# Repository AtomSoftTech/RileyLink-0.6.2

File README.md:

# RileyLink-0.6.2

Basically a newer version of : https://github.com/ps2/rileylink/tree/master/hardware

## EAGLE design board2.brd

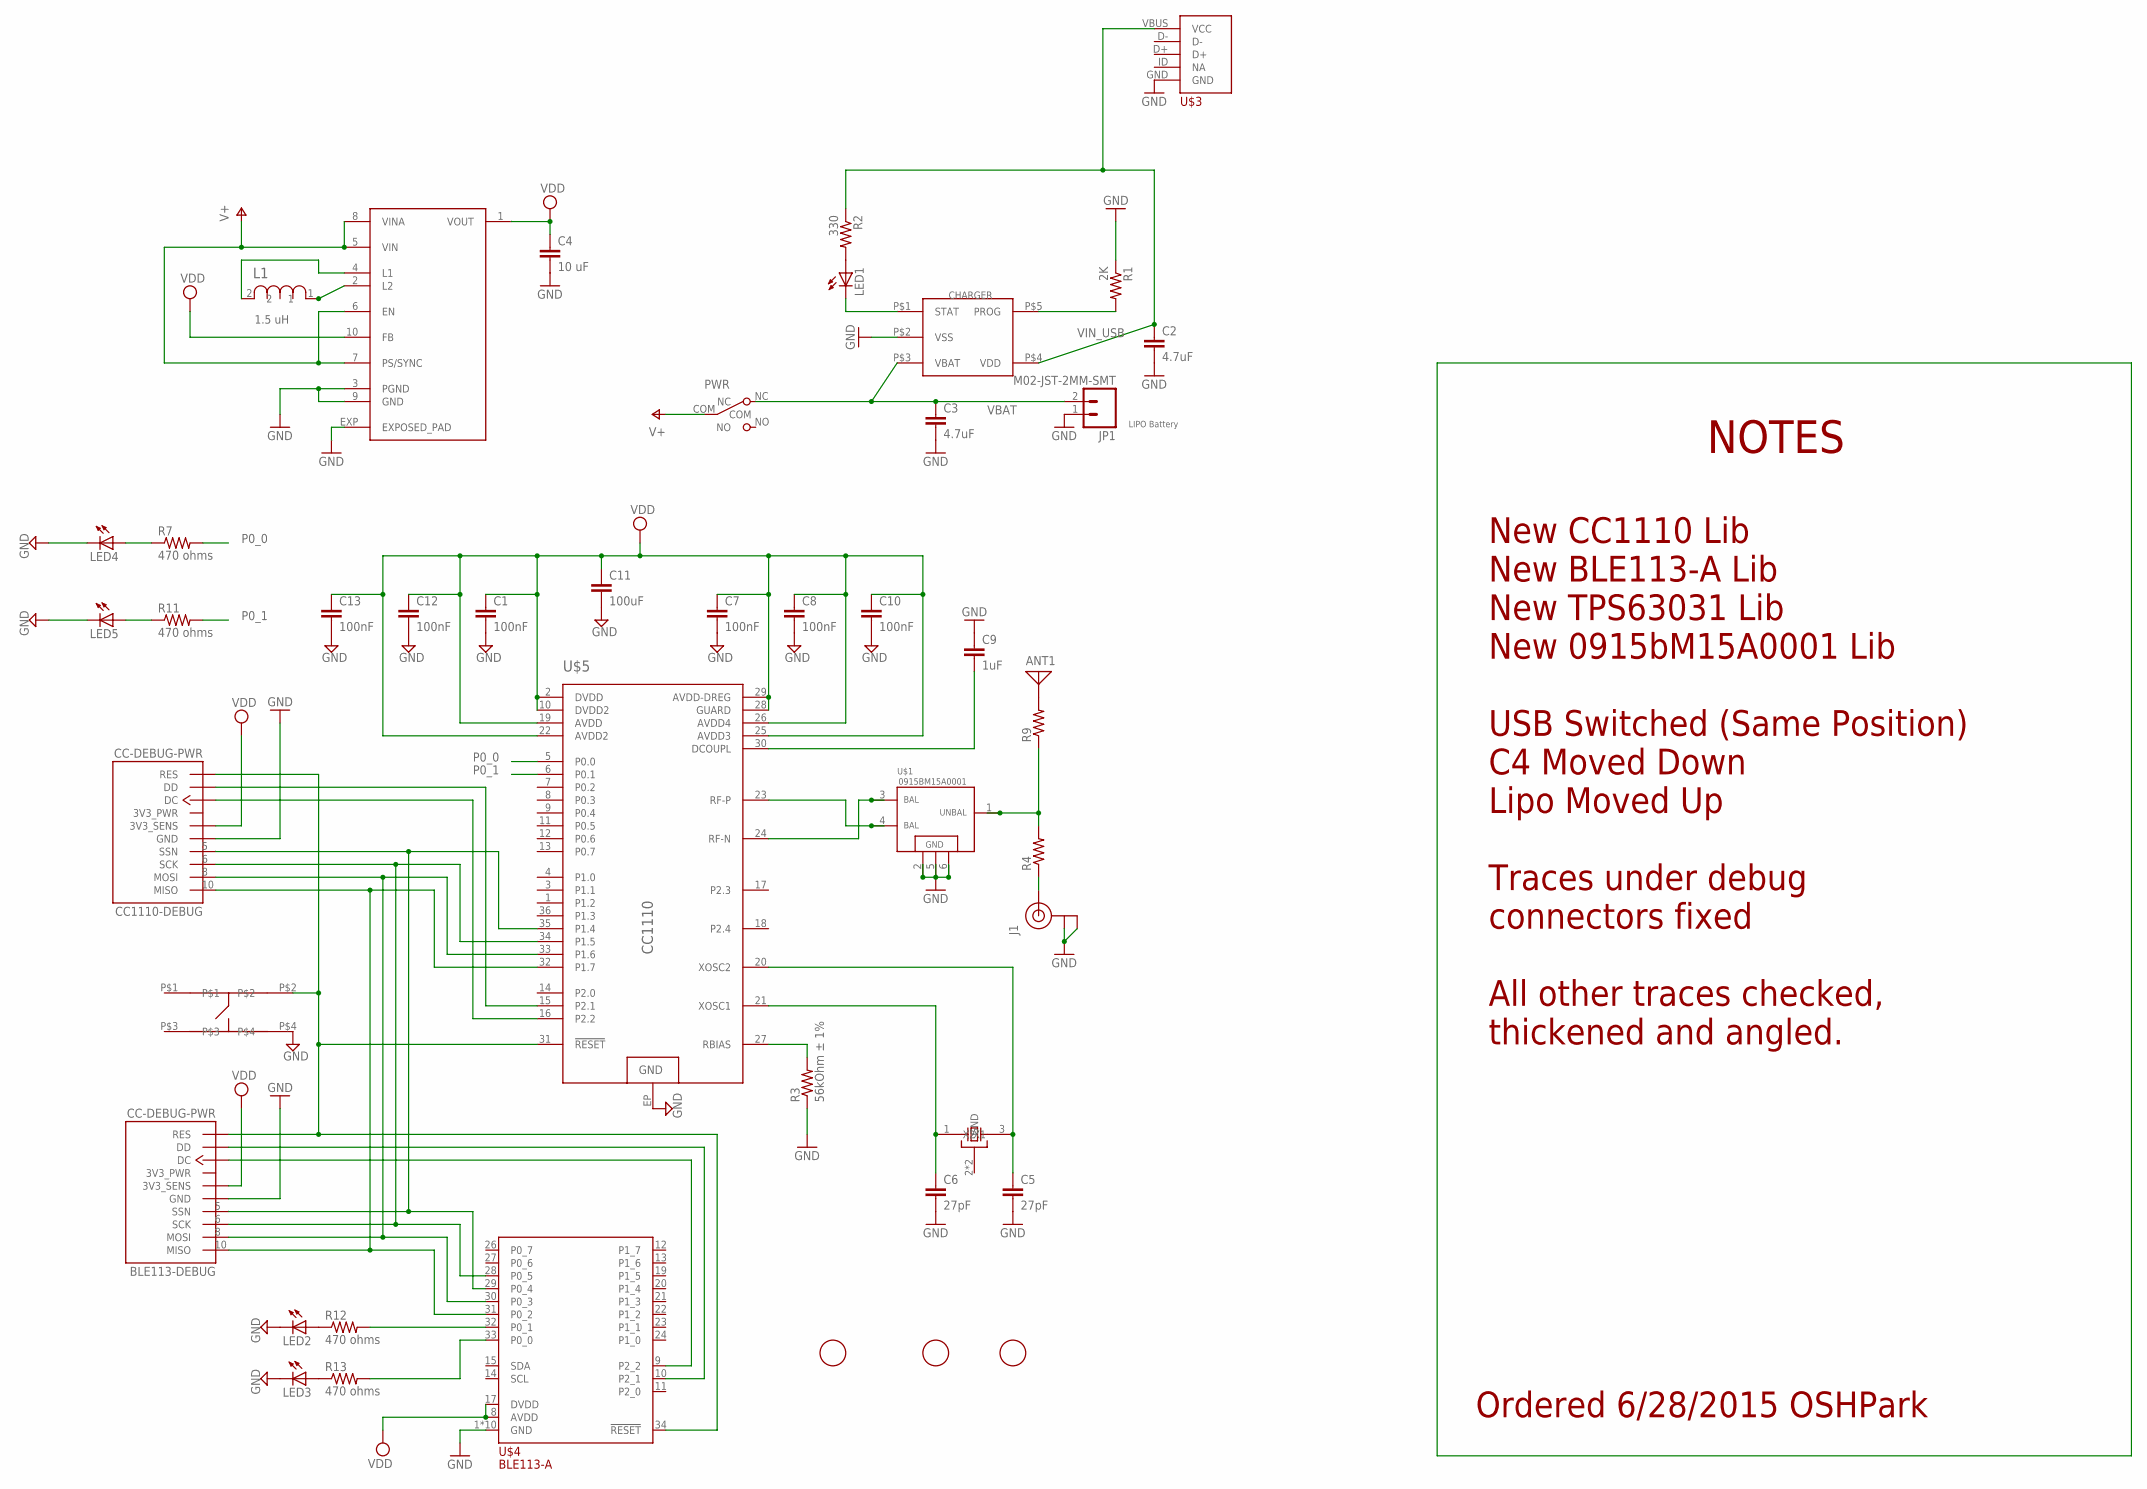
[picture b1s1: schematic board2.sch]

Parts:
ANT1: ANTENNA; PAD-01
BLE113-DEBUG: CC-DEBUG-PWR; CC-P05
C1, C7, C8, C10, C12, C13: 100nF; C0402
C2: 4.7uF; C0402K
C3: 4.7uF; C0603K
C4: 10 uF; C0805K
C5, C6: 27pF; C0402K
C9: 1uF; C0402K
C11: 100uF; C0402
CC1110-DEBUG: CC-DEBUG-PWR; CC-P05
CHARGER: MCP73831; 5PIN_SOT23
FID1, FID2, FID3: FIDUCIAL; FIDUCIAL_1MM
J1: U.FL
JP1: M02-JST-2MM-SMT; JST-2-SMD
L1: 1.5 uH; INDC1610X12N
LED1, LED2, LED3, LED4, LED5: LEDSML0603; SML0603
PWR: SW_SLIDE; SLIDE_SWITCH_SMD
R1: 2K; R0402
R2: 330; R0402
R3: 56kOhm ± 1%; R0402
R4, R9: R-US_R0402; R0402
R7, R11, R12, R13: 470 ohms; R0402
U$1: 0915BM15A0001_BANDPASS; 0915BM15A0001
U$2: TACTILE_SWITCH; PTS540
U$3: USB_GENERICMINI_B; USB_GENERIC
U$4: BLE113-A
U$5: CC1110; QFN36
U$6: TPS63031; 10SON
X1: 26MHz 10pF 10ppm -20C +70C; CTS_32X25

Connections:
DC: CC1110-DEBUG.3 (DC), U$5.16 (P2.2)
DC_BLE: BLE113-DEBUG.3 (DC), U$4.9 (P2_2)
DD: CC1110-DEBUG.4 (DD), U$5.15 (P2.1)
DD_BLE: BLE113-DEBUG.4 (DD), U$4.10 (P2_1)
GND: BLE113-DEBUG.1 (GND), C1.2, C2.2, C3.2, C4.2, C5.2, C6.2, C7.2, C8.2, C9.1, C10.2, C11.2, C12.2, C13.2, CC1110-DEBUG.1 (GND), CHARGER.P$2 (VSS), J1.P$1 (GND), J1.P$2 (GND), JP1.1 (2), LED2.C, LED3.C, LED4.C, LED5.C, R1.1, R3.1, U$1.2, U$1.5, U$1.6, U$2.P$4, U$3.GND, U$4.1 (GND), U$4.2 (GND), U$4.3 (GND), U$4.4 (GND), U$4.5 (GND), U$4.6 (GND), U$4.7 (GND), U$4.18 (GND), U$4.25 (GND), U$4.36 (GND), U$5.EP (GND2), U$6.3 (PGND), U$6.9 (GND), U$6.EXP (EXPOSED_PAD), X1.2 (GND), X1.4 (GND)
MISO: BLE113-DEBUG.10 (MISO), CC1110-DEBUG.10 (MISO), U$4.31 (P0_2), U$5.32 (P1.7)
MOSI: BLE113-DEBUG.8 (MOSI), CC1110-DEBUG.8 (MOSI), U$4.30 (P0_3), U$5.33 (P1.6)
unnamed: L1.1, U$6.2 (L2)
unnamed: CHARGER.P$1 (STAT), LED1.C
unnamed: CHARGER.P$5 (PROG), R1.2
unnamed: LED1.A, R2.2
unnamed: U$1.3, U$5.24 (RF-N)
unnamed: L1.2, U$6.4 (L1)
unnamed: U$1.4, U$5.23 (RF-P)
unnamed: J1.P$3 (SIGNAL), R4.1
unnamed: R4.2, R9.1, U$1.1
unnamed: ANT1.1, R9.2
unnamed: R3.2, U$5.27 (RBIAS)
unnamed: C9.2, U$5.30 (DCOUPL)
unnamed: C6.1, U$5.21 (XOSC1), X1.1 (X1)
unnamed: C5.1, U$5.20 (XOSC2), X1.3 (X2)
unnamed: LED4.A, R7.1
unnamed: LED5.A, R11.1
unnamed: LED2.A, R12.1
unnamed: LED3.A, R13.1
unnamed: R12.2, U$4.32 (P0_1)
unnamed: R13.2, U$4.33 (P0_0)
P0_0: R7.2, U$5.5 (P0.0)
P0_1: R11.2, U$5.6 (P0.1)
RESET: BLE113-DEBUG.7 (RES), CC1110-DEBUG.7 (RES), U$2.P$2, U$4.34 (!RESET!), U$5.31 (!RESET)
SCK: BLE113-DEBUG.6 (SCK), CC1110-DEBUG.6 (SCK), U$4.28 (P0_5), U$5.34 (P1.5)
SSN: BLE113-DEBUG.5 (SSN), CC1110-DEBUG.5 (SSN), U$4.29 (P0_4), U$5.35 (P1.4)
V+: PWR.COM, U$6.5 (VIN), U$6.6 (EN), U$6.7 (PS/SYNC), U$6.8 (VINA)
VBAT: C3.1, CHARGER.P$3 (VBAT), JP1.2 (1), PWR.NC
VDD: BLE113-DEBUG.2 (3V3_SENS), C1.1, C4.1, C7.1, C8.1, C10.1, C11.1, C12.1, C13.1, CC1110-DEBUG.2 (3V3_SENS), U$4.8 (AVDD), U$4.17 (DVDD), U$5.2 (DVDD), U$5.10 (DVDD2), U$5.19 (AVDD), U$5.22 (AVDD2), U$5.25 (AVDD3), U$5.26 (AVDD4), U$5.28 (GUARD), U$5.29 (AVDD-DREG), U$6.1 (VOUT), U$6.10 (FB)
VIN_USB: C2.1, CHARGER.P$4 (VDD), R2.1, U$3.VBUS (VCC)

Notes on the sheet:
LIPO Battery
Ordered 6/28/2015 OSHPark
NOTES
New CC1110 Lib New BLE113-A Lib New TPS63031 Lib New 0915bM15A0001 Lib
USB Switched (Same Position) C4 Moved Down Lipo Moved Up
Traces under debug connectors fixed
All other traces checked, thickened and angled.

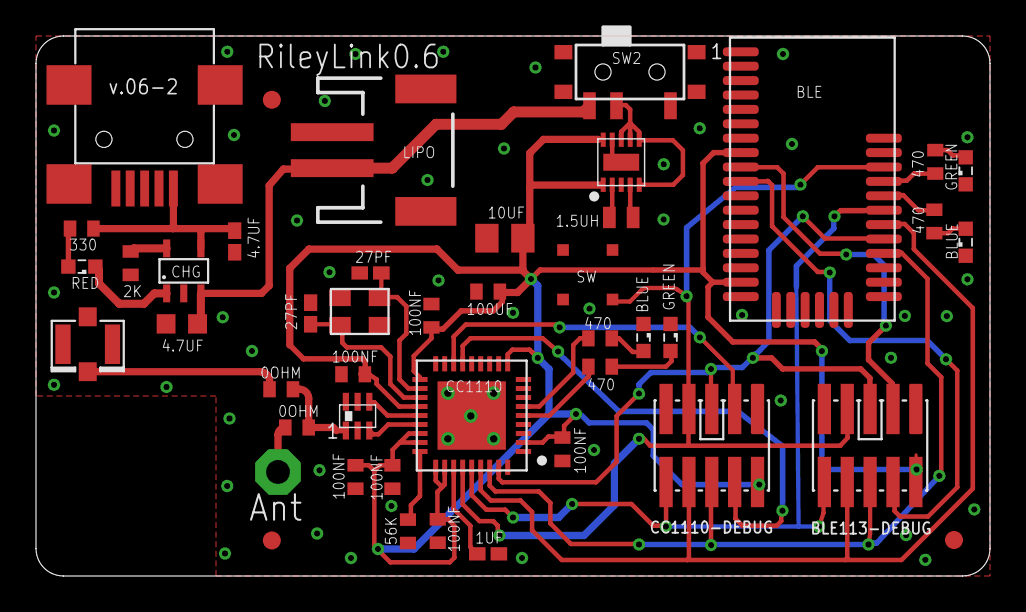
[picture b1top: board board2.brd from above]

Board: 2 copper layers, 53.0 x 30.0 mm, 45 parts (0 on the bottom side), 36 nets.

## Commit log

2015-06-28 :confetti_ball: Added .gitattributes & .gitignore files
2015-06-28 upd1
2015-06-28 First
2015-06-28 added library
2015-06-28 No Hex
2015-06-28 notes n no backup
2015-06-28 New Notes
2015-06-28 cleaner
2015-06-28 cough
2015-07-25 AtomIzed

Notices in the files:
parts and their libraries:
parts: Package design from "pretty-eagle-libs" at https://github.com/esden/pretty-eagle-libs/blob/master/pel_misc.lbr by @esden at Github. (CC-BY-SA-3.0)
SparkFun-Connectors: Licensing: Creative Commons ShareAlike 4.0 International - https://creativecommons.org/licenses/by-sa/4.0
